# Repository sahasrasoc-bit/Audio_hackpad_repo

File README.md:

***Sahasra’s Audio Hackpad***
-------------------------------------

**Inspiration**
--
One of the biggest problems I always face when audio editing is having the shortcuts and keys that I used far part. This meant that even for repeatative actions, I had to many times take my hand off the mouse and click delete, or move my hand across the whole keyboard. This slowed down my editing process extrmely, and since the keys are so far apart, I often click the wrong buttons (destroying whatever file/rpoject I was wroking on). This hackpad is designed to solve that problem, as I specifically designed it for audio editing, allowing me to quickly cut audio and adjust noise levels (all referencing Adobe Audition). Moreover, I can do all this without risking clicking the wrong button or moving my hand away from my mouse, solving my problem with time constraints and incorrect commands.  

**Challenges**
--
This was my very first time doing anything like this project. That means first-time using PCBs, electrical schematics, GitHub, the whole gist.  It took a lot of googling and asking others for help, but I finally made it after a couple of weeks.  I'm really proud of this finished product and super happy that it'll solve a lot of my audio editing problems now. The most trouble I faced was with the resources, as many times they were extremely vauge, so I had to figure out how to work everything out from the beginning (making me take longer than the average person). 

**Specifications and BOM**
--
**Bill of Materials**
|Material| Count|
| -------- | -------- | 
| Cherry MX Switches | 5 | 
| EC11 Rotary Encoder | 1 | 
| XIAO RP2040 | 1 | 
| Blank DSA Keycaps| 5 | 
| M3x16 Bolt | 4 | 
| M3 Heatset| 4| 
| Custom PCB | 1 | \

\
Others: - KMK Firmware - Top Case.stl  - Bottom Case.stl - Custom PCB
\
*All of these parts I already own, so nothing needed for purchase*

**Schematic**
--

**PCB**
--

**Case**
--

**Firmware**
--
Firmware was done using the template provided by blueprint using kmk. The changes made to the code included assigning each key to the board and adding in what each key did, heavily refrencing the shortcuts given in the library. 

**Resources Used**
--
Took a lot of inspiration from this guide from Blueprint! However, it was quite vague in terms of the additional features I wanted to add, so I used a lot of youtube videos as well. 
\
Blueprint Guide: https://blueprint.hackclub.com/hackpad/index.md
\
Youtube  KiCAD Starter guide: https://www.youtube.com/watch?v=d9_-lQq8ShE 
\
PCB Design tutorials: https://www.youtube.com/watch?v=zeH3WbMWvdg
\
People from slack + a LOT more Phil's Lab videos

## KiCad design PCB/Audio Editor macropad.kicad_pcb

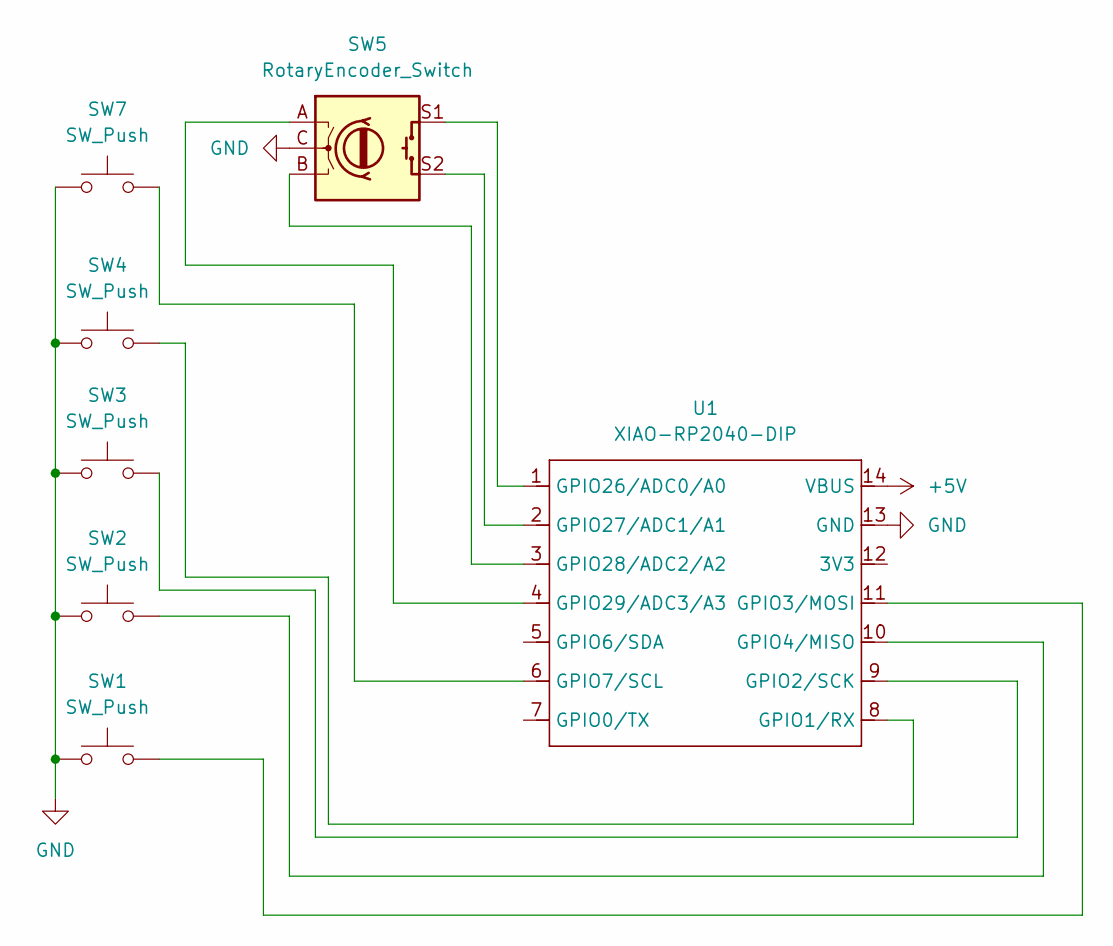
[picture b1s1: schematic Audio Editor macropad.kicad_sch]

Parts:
SW1, SW2, SW3, SW4, SW7: SW_Push; SW_Cherry_MX_1.00u_PCB
SW5: RotaryEncoder_Switch; RotaryEncoder_Alps_EC11E-Switch_Vertical_H20mm
U1: XIAO-RP2040-DIP

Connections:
+5V: U1.14 (VBUS)
GND: SW1.1, SW2.1, SW3.1, SW4.1, SW5.C, SW7.1, U1.13 (GND)
unnamed: SW4.2, U1.8 (GPIO1/RX)
unnamed: SW3.2, U1.9 (GPIO2/SCK)
unnamed: SW1.2, U1.11 (GPIO3/MOSI)
unnamed: SW2.2, U1.10 (GPIO4/MISO)
unnamed: SW7.2, U1.6 (GPIO7/SCL)
unnamed: SW5.S1, U1.1 (GPIO26/ADC0/A0)
unnamed: SW5.S2, U1.2 (GPIO27/ADC1/A1)
unnamed: SW5.B, U1.3 (GPIO28/ADC2/A2)
unnamed: SW5.A, U1.4 (GPIO29/ADC3/A3)

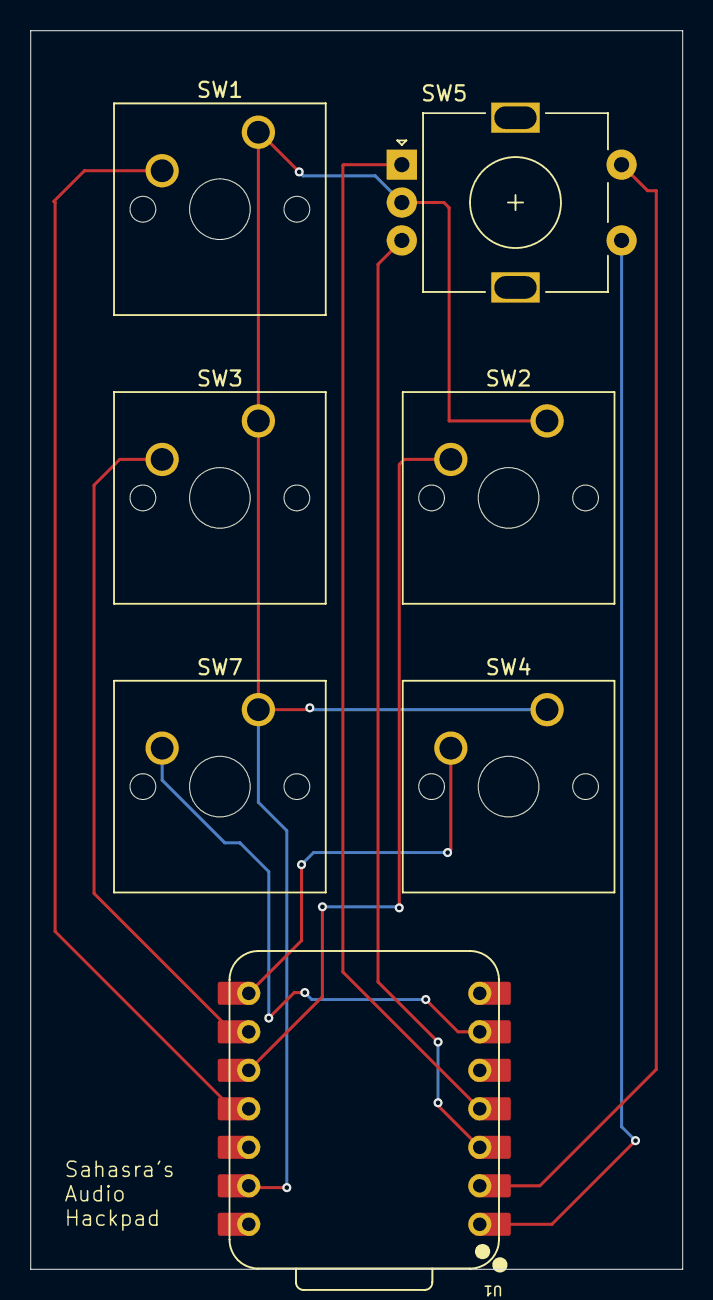
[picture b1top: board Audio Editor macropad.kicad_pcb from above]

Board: 2 copper layers, 43.0 x 81.7 mm, 7 parts (0 on the bottom side), 10 nets.

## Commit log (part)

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2026-01-21 Initial Commit
    Initial Commit
2026-01-21 Moved everything out
2026-01-22 Added necessary PCB files
2026-01-22 Correct File Positions
2026-01-22 Corrected Project Files
2026-01-22 Positioning Files
2026-01-22 Added README
2026-01-22 Clean-up files
2026-06-16 Update ModifedStarterCode
2026-06-17 Added Gerber files
2026-06-17 Added Gerber files for PCB
2026-06-17 With components added
